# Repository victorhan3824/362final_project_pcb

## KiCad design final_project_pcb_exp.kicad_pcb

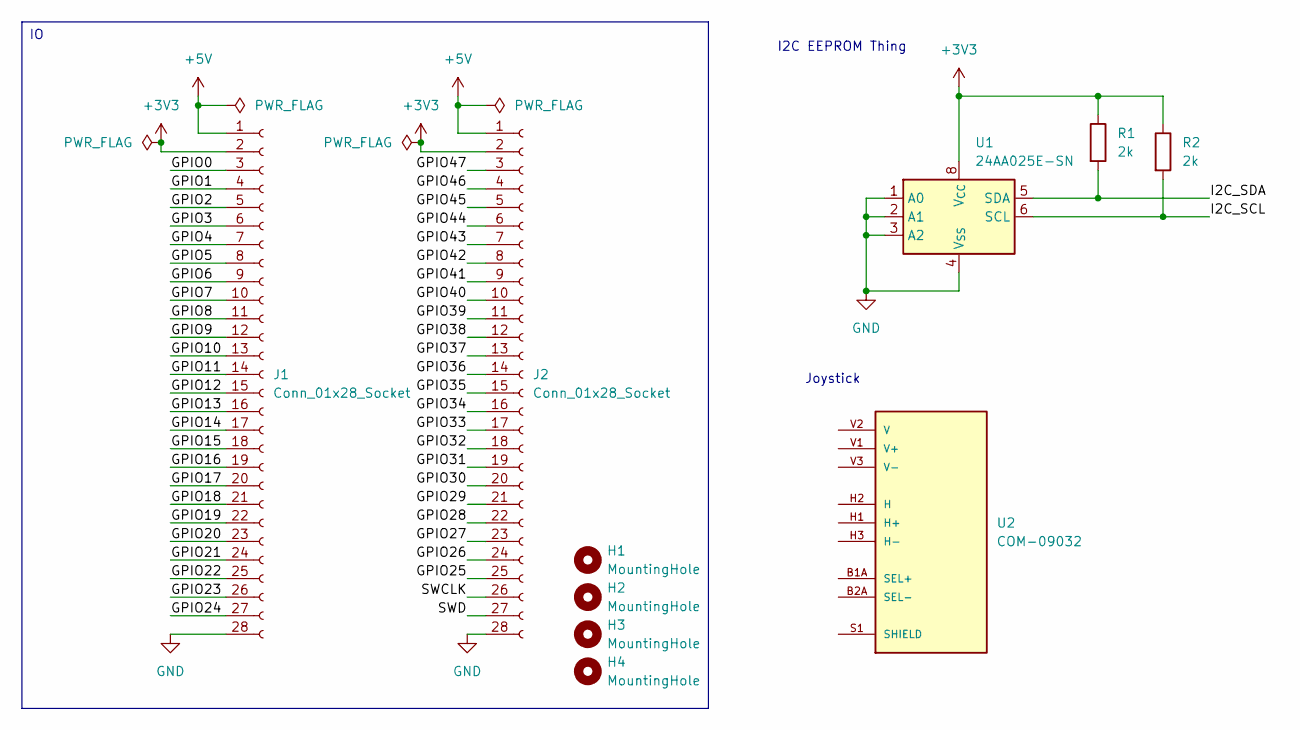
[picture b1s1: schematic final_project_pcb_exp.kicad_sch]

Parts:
H1, H2, H3, H4: MountingHole; MountingHole_2.5mm
J1, J2: Conn_01x28_Socket; PinSocket_1x28_P2.54mm_Vertical
R1, R2: 2k; R_0805_2012Metric
U1: 24AA025E-SN; DIP-8_W7.62mm
U2: COM-09032; XDCR_COM-09032; PARTREV N/A

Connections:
+3V3: J1.2, J2.2, R1.1, R2.1, U1.8 (V_{CC})
+5V: J1.1, J2.1
/GPIO0: J1.3
/GPIO1: J1.4
/GPIO2: J1.5
/GPIO3: J1.6
/GPIO4: J1.7
/GPIO5: J1.8
/GPIO6: J1.9
/GPIO7: J1.10
/GPIO8: J1.11
/GPIO9: J1.12
/GPIO10: J1.13
/GPIO11: J1.14
/GPIO12: J1.15
/GPIO13: J1.16
/GPIO14: J1.17
/GPIO15: J1.18
/GPIO16: J1.19
/GPIO17: J1.20
/GPIO18: J1.21
/GPIO19: J1.22
/GPIO20: J1.23
/GPIO21: J1.24
/GPIO22: J1.25
/GPIO23: J1.26
/GPIO24: J1.27
/GPIO25: J2.25
/GPIO26: J2.24
/GPIO27: J2.23
/GPIO28: J2.22
/GPIO29: J2.21
/GPIO30: J2.20
/GPIO31: J2.19
/GPIO32: J2.18
/GPIO33: J2.17
/GPIO34: J2.16
/GPIO35: J2.15
/GPIO36: J2.14
/GPIO37: J2.13
/GPIO38: J2.12
/GPIO39: J2.11
/GPIO40: J2.10
/GPIO41: J2.9
/GPIO42: J2.8
/GPIO43: J2.7
/GPIO44: J2.6
/GPIO45: J2.5
/GPIO46: J2.4
/GPIO47: J2.3
/I2C_SCL: R2.2, U1.6 (SCL)
/I2C_SDA: R1.2, U1.5 (SDA)
/SWCLK: J2.26
/SWD: J2.27
GND: J1.28, J2.28, U1.1 (A0), U1.2 (A1), U1.3 (A2), U1.4 (V_{SS})
unnamed: U2.S1 (SHIELD), U2.S2 (SHIELD), U2.S3 (SHIELD), U2.S4 (SHIELD)

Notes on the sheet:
Joystick
I2C EEPROM Thing

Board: 2 copper layers, 10 parts (0 on the bottom side), 6 nets, no tracks yet.
